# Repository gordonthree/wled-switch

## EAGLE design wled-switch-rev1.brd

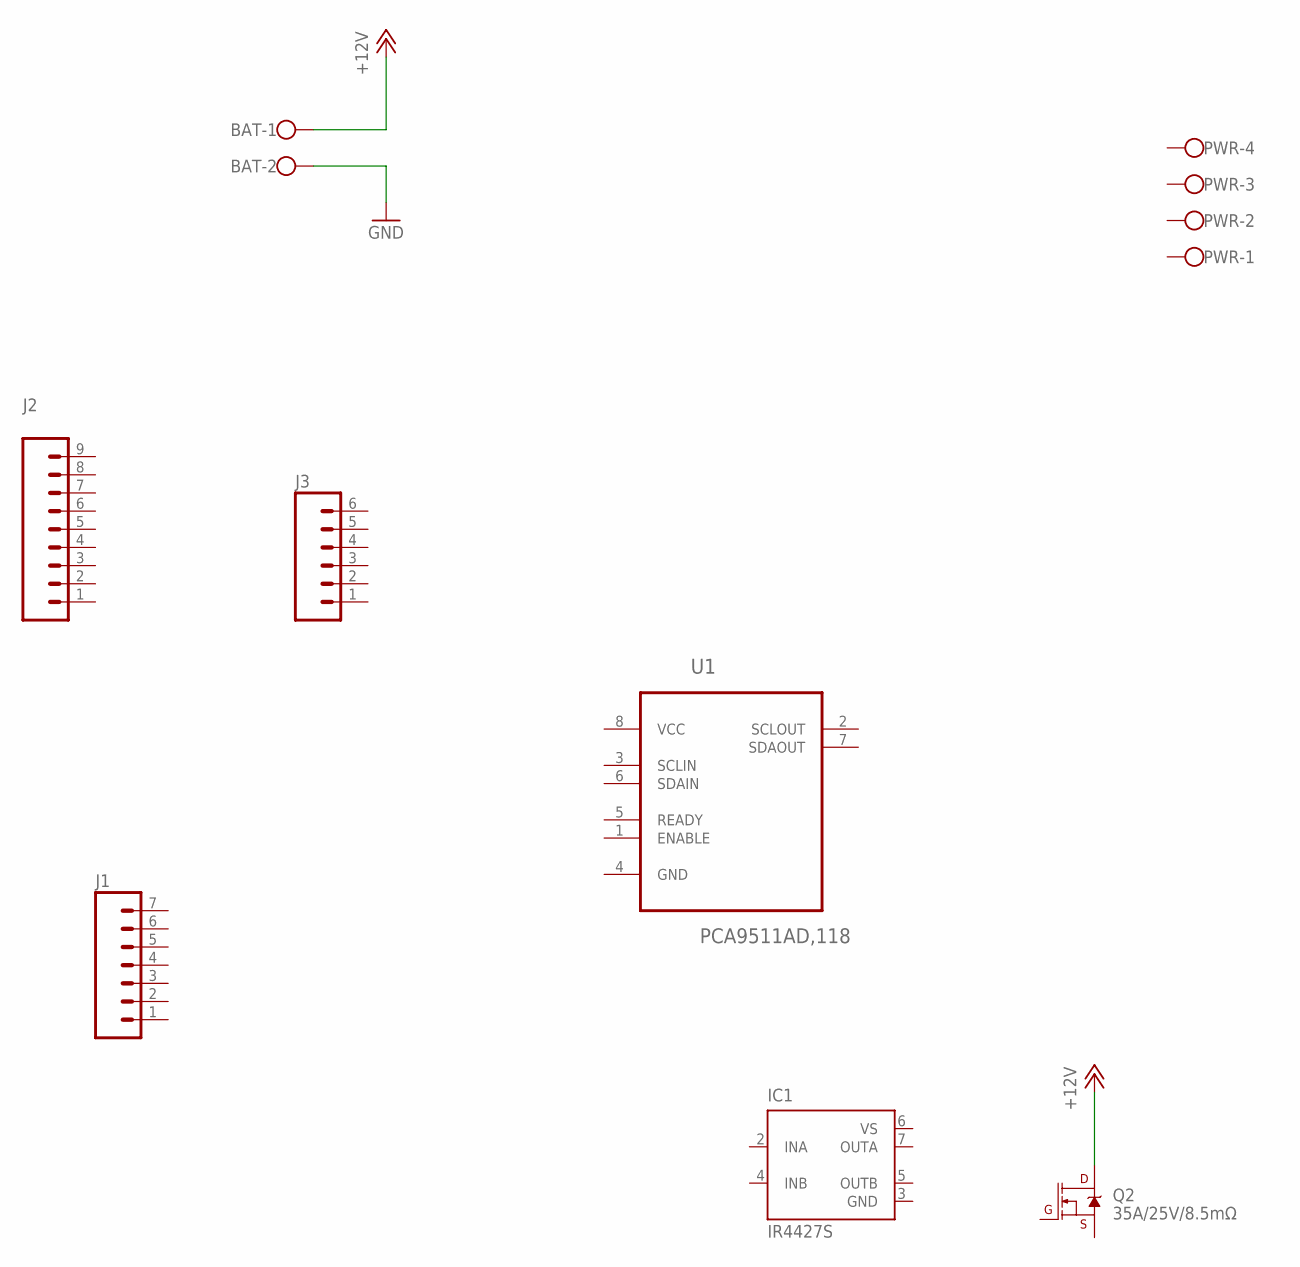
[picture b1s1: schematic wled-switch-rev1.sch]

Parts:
BAT: W237-102
IC1: IR4427S; SO08
J1: M07; 1X07
J2: M09; 1X09
J3: M06SILK_FEMALE_PTH; 1X06
PWR: W237-4
Q2: 35A/25V/8.5mΩ; TO-252/DPAK
U1: PCA9511AD,118; SOIC127P600X175-8N

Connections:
+12V: BAT.1, Q2.2 (D)
GND: BAT.2, IC1.3 (GND)
VCC: U1.8 (VCC)
VS: IC1.6 (VS)

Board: 2 copper layers, 8 parts (0 on the bottom side), 2 nets, no tracks yet.

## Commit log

2022-09-09 added gitignore
2022-09-09 rough draft...

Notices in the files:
parts and their libraries:
SparkFun-Connectors: Licensing: Creative Commons ShareAlike 4.0 International - https://creativecommons.org/licenses/by-sa/4.0
